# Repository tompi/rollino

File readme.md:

Rollino
=======

An attempt to make a cheap, solid and low profile DIY finger trackball.

The ball floats just 1 mm above the table on three ceramic support balls.
Two PMW3610 sensors look up at the ball from below its equator, placed so
their lines of sight are orthogonal (X, Y and twist are all observable);
their boards lie on their sides in a low ring round the back half of the
ball, each behind a printed cover that follows the ball and has a window for
the lens. A Seeed XIAO nRF52840 running ZMK lies flat in a low pod that swells out of the rim in front of
the ball, soldered upside down onto a base PCB that sits in a groove in the
underside; an FPC ribbon runs from each sensor board to it. The 602020 LiPo
stands in the same ring, between the two sensors and away from the XIAO's
antenna, leaning against the ball at the sensor boards' tilt; its leads run
round in a groove. A cover, a separate printed part, closes the whole
underside (the battery's pocket included), held by six screws.

- `case/rollino.scad` - parametric OpenSCAD model (ball size, sensor/MCU
  placement, battery, ...). Set `part` to `assembly`, `exploded`, `hardware`, `section`,
  or `body` / `base_cover` / `sensor_cover` (print two) for the printable
  parts. `fpc_check`, `wall_check` and `usb_check` should come out empty:
  there is room to pull the ribbons through, no cavity comes too close to
  the outside (`wall_check` does show the open end of the USB plug's recess),
  and the biggest USB-C plug the spec allows (12.35 x 6.5 mm overmold) goes
  in, 0.35 mm clear of the table.
- `case/renders/` - preview renders: `case/render_previews.sh` (OpenSCAD) and
  `case/render_exploded.sh` (Blender, with KiCad's 3D models of the boards:
  the assembled and the exploded view).
- `pcb/` - KiCad projects for the sensor boards and the base board: schematics
  and routed boards, generated from the case model (see [pcb/readme.md](pcb/readme.md)).

- [parts.md](parts.md) - everything to order for one Rollino.
- `datasheets/` - component datasheets. The PMW3610 datasheet is available
  [here](https://www.epsglobal.com/Media-Library/EPSGlobal/Products/files/pixart/PMW3610DM-SUDU.pdf?ext=.pdf).

Firmware
--------

ZMK, built by GitHub Actions on every push (download `firmware.zip` from the
run, then double-tap the XIAO's reset and copy the `.uf2` onto it: its
button faces down, and the cover has a hole under it for a paper clip). It's
a standalone Bluetooth/USB mouse.

- `zmk/boards/shields/rollino/` - the shield: pins, the two PMW3610 sensors
  (Zephyr's driver), three optional buttons.
- `zmk/src/ball_fusion.c` - combines the two sensors: each one only sees the
  ball's surface sliding past in its own tilted plane; together they give the
  ball's whole rotation. Rolling moves the pointer (as if the finger on top
  dragged it), twisting about the vertical axis scrolls.
- `config/rollino.keymap` - the buttons: left, middle, right click.

**Bluetooth profiles, without buttons.** It keeps three profiles (hosts).
Wiggle the ball - twist it quickly back and forth, a flick of about 20
degrees each way, with no pause - and it acts when you stop:

- 6 to 11 flicks (about a second): switch to the next profile. One that has
  no host yet advertises, so a new computer can pair with it.
- 12 or more (two seconds or so): forget the current profile's host and
  advertise again, to pair it afresh.

Scrolling stops from the fourth flick, so the page doesn't jump about.
Slow scrolling back and forth never adds up to a gesture (a flick more
than 0.4 s after the last starts the count again). The thresholds are the
`gesture-*` properties of the shield's `ball_fusion` node. To forget every
host at once, flash the `settings_reset` firmware from the same build, then
`rollino` again.

| XIAO pin | Use |
|----------|-----|
| D4 | SCLK, both sensors |
| D5 | SDIO, both sensors (SPI MOSI and MISO on the same pin) |
| D7 | NCS, right sensor |
| D6 | NCS, left sensor |
| D8 | MOTION, right sensor |
| D2 | MOTION, left sensor |
| D0, D1, D9 | optional buttons to GND: left, middle, right click |
| D3, D10 | free |

**Calibrating the sensors' orientation.** The fusion needs to know which way
each sensor's X axis points (`rotation` in the shield's `ball_fusion` node,
plus the sensor's `invert-x` / `invert-y`), which depends on how the chip
sits on the sensor PCB. The two boards are the same, lying on their sides
and turned half a turn from each other, so the two rotations differ by 180
(90 and 270 to start with). Roll the ball right: the pointer should go right;
towards you: down; twist it: scroll, with no drift. If one direction is off,
try one sensor at a time (cover the other's lens) and fix its rotation /
inversion until rolling right moves the pointer mostly right.

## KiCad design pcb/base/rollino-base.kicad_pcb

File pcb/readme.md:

Rollino PCBs
============

Two KiCad 8 projects, generated from the case model: board outlines, and
where the XIAO, the FPC connectors and the screw holes go, all come from
`case/rollino.scad`.

Rebuild them after changing the case (KiCad's own Python; Freerouting 1.5,
Java, Blender 3.x and ImageMagick for routing and rendering):

```
PY=/Applications/KiCad/KiCad.app/Contents/Frameworks/Python.framework/Versions/Current/bin/python3
$PY pcb/gen/generate.py     # schematics, footprints placed on their nets, the tracks that matter laid
$PY pcb/gen/route.py        # Freerouting routes the rest, GND poured on both layers and stitched
pcb/gen/render_pcbs.sh      # the renders above, the layout images and schematic PDFs
```

They overwrite the projects, so make changes in the scripts rather than the
KiCad files, or stop using them once you start editing the boards by hand.

Both boards are routed (0.2 mm tracks, wider where it matters, 0.15 mm
clearance, 0.3 mm from the edges, 0.6/0.3 mm vias) and pass DRC with nothing
to report, warnings included (`kicad-cli pcb drc --schematic-parity
--severity-all`); the schematics pass ERC. `route.py` checks that itself: it
only saves a board with nothing left unconnected and nothing for the DRC to
report, and fails otherwise. The sensor board's references are on its fab
layer only, as are the base board's test points' (their labels name them):
the silkscreen has no room for them.

Freerouting 1.5 can't start a track from the base board's FPC connectors
(their pads are 10 degrees off the board's axes) and would leave them
unconnected, so `generate.py` lays a short track out of each pad and
`route.py` has Freerouting join those up instead.

Sensor board (`sensor/`, two needed)
--------------------------------------

[Schematic (PDF)](sensor/rollino-sensor-schematic.pdf)

The same board for both sensors. It lies on its side (the chip's long axis
horizontal, the connector end towards the front of the case), so the left
one is turned half a turn from the right one. It's screwed into its pod from
the ball side with two M2 screws, chip side out, lens towards the ball; the
case's pocket matches its outline, ear included, and a printed cover with a
window for the lens goes in on top of it, under the same two screws.

- PMW3610DM-SUDU + LM18-LSI lens: circuit and footprint (with the lens cutout)
  after [badjeff/pmw3610-pcb](https://github.com/badjeff/pmw3610-pcb)
  (CERN-OHL-P-2.0)
- TPS7A0518 1.8 V LDO for the sensor's core: 1 uA quiescent, instead of the
  ~34 uA of the TLV74318 used there, which would otherwise draw more than the
  resting sensor
- each capacitor is by the pin it serves, on a short wide track laid by
  `generate.py`: C4 under the charge pump's two pins and C6/C7 under VCP's
  (PixArt asks for those tracks to be under 5 mm long and over 20 mil wide:
  they are 2 to 4 mm and 0.6 mm), C5 under the laser's, C2/C1 under VDD's,
  C8/C3 by VDDIO's and C9 against the regulator's output; their grounds are
  a rail from pin 11 with vias to the pour on the back
- 1.8 V goes from the regulator to VDD on the back, round the lens cutout's
  short end
- TP1 (+1V8) and TP2 (GND): pads for a meter when bringing a board up
- FH12-6S-0.5SH FPC connector at the board's front end, mouth facing off
  the edge, so the ribbon is easy to push in and latch before the board goes
  into its pod; the ribbon then bends back over the connector and the chip,
  where it is folded (a 45 degree crease, flat) to run down the slope, past
  the board's low edge, to the base board (the pod has room for the bend and
  a channel for the ribbon)
- two mounting holes either side of the lens: H1 in an ear on the back end,
  on the board's centre line, and H2 beside the connector. Nothing sticks
  out of one long side only, so the board fits either way up the slope
- the ribbon's way down through the pod is roomy (5.5 mm wide, the case
  checks it with a 1.5 mm thick stand-in: `part="fpc_check"` must be empty),
  so its free end can be fed through from the pod or from underneath before
  the boards go in
- the regulator's EN is tied to its VIN by a fixed track between its rows of
  pins (route.py keeps it): the board edge leaves no other way in
- a small ROLLINO logo in bare copper on the back, between the front edge
  and the lens
- board frame: origin on the optical axis, x along the chip (towards the
  back of the case), y across it

Base board (`base/`)
--------------------

[Schematic (PDF)](base/rollino-base-schematic.pdf)

Lies in a groove in the case's underside, under the front pod and a little
way round each side, held (with the cover under it) by four M2 screws.

- Seeed XIAO nRF52840 soldered **upside down** by its castellated edges: its
  parts (USB-C included) hang through the cutout into a pocket in the cover;
  its battery pads face up, and the LiPo's leads (which come round from the
  battery's pocket in the ring at the back of the case, and up behind the XIAO's far
  corner) solder straight onto them
- J1 (right sensor) and J2 (left) at the band's ends, along it, mouths facing
  the ribbons coming along the channel in the case's underside
- J3-J5: optional buttons (left, middle, right click), a pair of through
  holes each (2.54 mm apart, for wires or a header): the square one the
  button's line, the round one GND. Left and right on the branches, in
  front of the screws; middle beside the XIAO's far left corner (the strip
  behind the XIAO is the antenna's)
- the ROLLINO logo is bare copper (no solder mask) on the back, beside the
  XIAO
- the XIAO's chip antenna is at its far end, inside the notch and a fraction
  of a millimetre from this board: the pours stay off the strip between the
  notch and the ball's hole and away from the XIAO's last few millimetres,
  and the four tracks that have to cross that strip (the bus and the supply,
  to the left sensor) keep a millimetre from the notch; the supply's two,
  the only thing joining the two halves' ground, are laid by `generate.py`
  on the back
- pins as in the firmware (`zmk/boards/shields/rollino/rollino.overlay`): the
  bus on D4/D5, the XIAO's only pins that aren't next to its radio, and each
  sensor's own lines and each button on the pins of their side

Ribbons
-------

Two 6-way 0.5 mm FFCs, 50 mm long (the stock length: 40 mm ones are hard
to find), with same-side (type A) contacts. Each leaves its sensor board's
connector towards the front, bends back over the connector and the chip, and
is folded there (a 45 degree crease, pressed flat) to run down the slope
over the chip's back. Past the board's low edge it turns in under the board,
lying on the cover, and with a second crease turns towards the front, along
a channel in the case's underside, straight into the base board's connector
at the end of the band; the case model sets where that is from the cable's
length (`fpc_len`). The U-turn, the fold and the crease each turn the ribbon
over, which leaves the face that met the sensor board's connector facing the
base board's: hence type A. The pins at each end are numbered from the
ribbon's path so that each signal meets itself: put the ribbon in, fold it
and lay it in its channel before the base board goes up.

Parts
-----

| Board | Ref | Part |
|-------|-----|------|
| sensor (x2) | U1 | PMW3610DM-SUDU + LM18-LSI lens |
| | U2 | TPS7A0518PDBVR (SOT-23-5) |
| | J1 | Hirose FH12-6S-0.5SH (or JUSHUO AFC01-S06FCA) |
| | R1 | 10k 0603 |
| | C1 | 3.3 uF 0603 |
| | C2, C3 | 100 nF 0603 |
| | C4 | 100 nF X7R 0603 |
| | C5 | 10 nF 0603 |
| | C6 | 10 uF X7R 0603 |
| | C7 | 10 nF X7R 0603 |
| | C8, C9 | 1 uF 0603 |
| base | U1 | Seeed XIAO nRF52840 (not Sense) |
| | J1, J2 | Hirose FH12-6S-0.5SH (or JUSHUO AFC01-S06FCA) |

`lib/` has the project's own symbols, footprints and 3D models (the XIAO's
from Seeed's, the PMW3610 and its lens as plain blocks); everything else is
from KiCad's standard libraries.

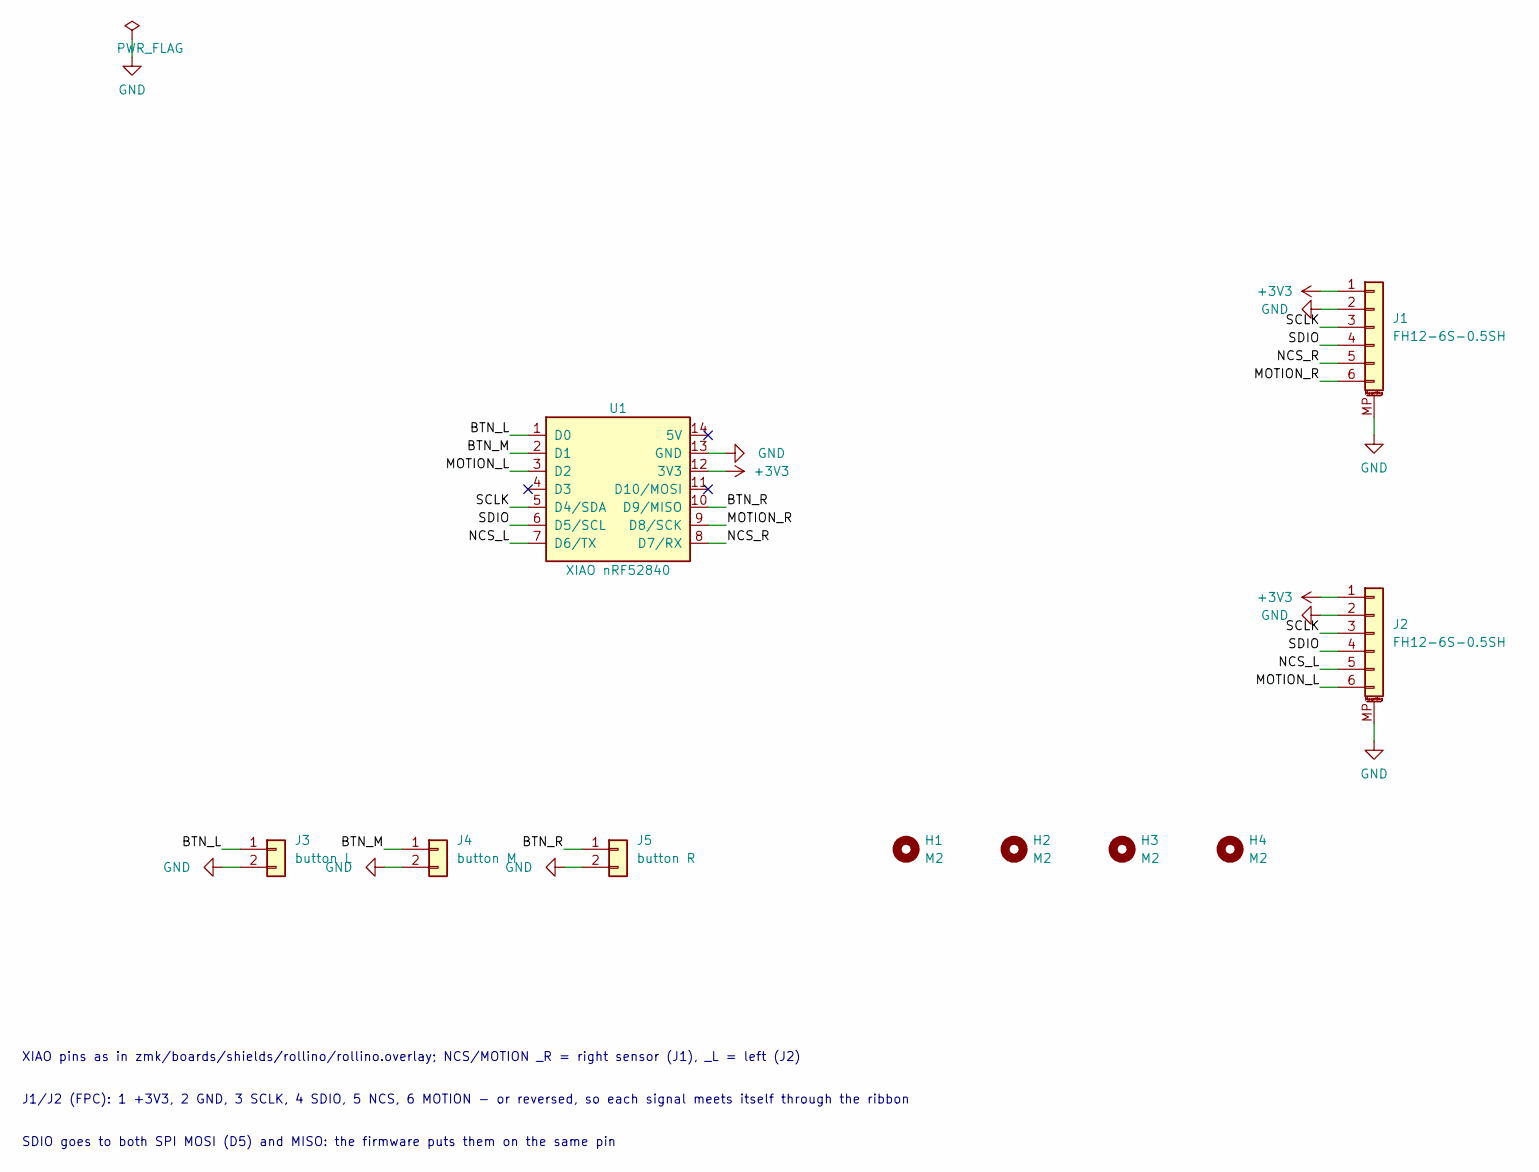
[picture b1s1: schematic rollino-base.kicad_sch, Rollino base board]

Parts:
H1, H2, H3, H4: M2; MountingHole_2.2mm_M2
J1, J2: FH12-6S-0.5SH; Hirose_FH12-6S-0.5SH_1x06-1MP_P0.50mm_Horizontal
J3: button L; ButtonPads_1x02_P2.54mm
J4: button M; ButtonPads_1x02_P2.54mm
J5: button R; ButtonPads_1x02_P2.54mm
U1: XIAO nRF52840; XIAO_nRF52840_upside_down

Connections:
+3V3: J1.1, J2.1, U1.12 (3V3)
/BTN_L: J3.1, U1.1 (D0)
/BTN_M: J4.1, U1.2 (D1)
/BTN_R: J5.1, U1.10 (D9/MISO)
/MOTION_L: J2.6, U1.3 (D2)
/MOTION_R: J1.6, U1.9 (D8/SCK)
/NCS_L: J2.5, U1.7 (D6/TX)
/NCS_R: J1.5, U1.8 (D7/RX)
/SCLK: J1.3, J2.3, U1.5 (D4/SDA)
/SDIO: J1.4, J2.4, U1.6 (D5/SCL)
GND: J1.2, J1.MP (MountPin), J2.2, J2.MP (MountPin), J3.2, J4.2, J5.2, U1.13 (GND)

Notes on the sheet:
XIAO pins as in zmk/boards/shields/rollino/rollino.overlay; NCS/MOTION _R = right sensor (J1), _L = left (J2)
J1/J2 (FPC): 1 +3V3, 2 GND, 3 SCLK, 4 SDIO, 5 NCS, 6 MOTION - or reversed, so each signal meets itself through the ribbon
SDIO goes to both SPI MOSI (D5) and MISO: the firmware puts them on the same pin

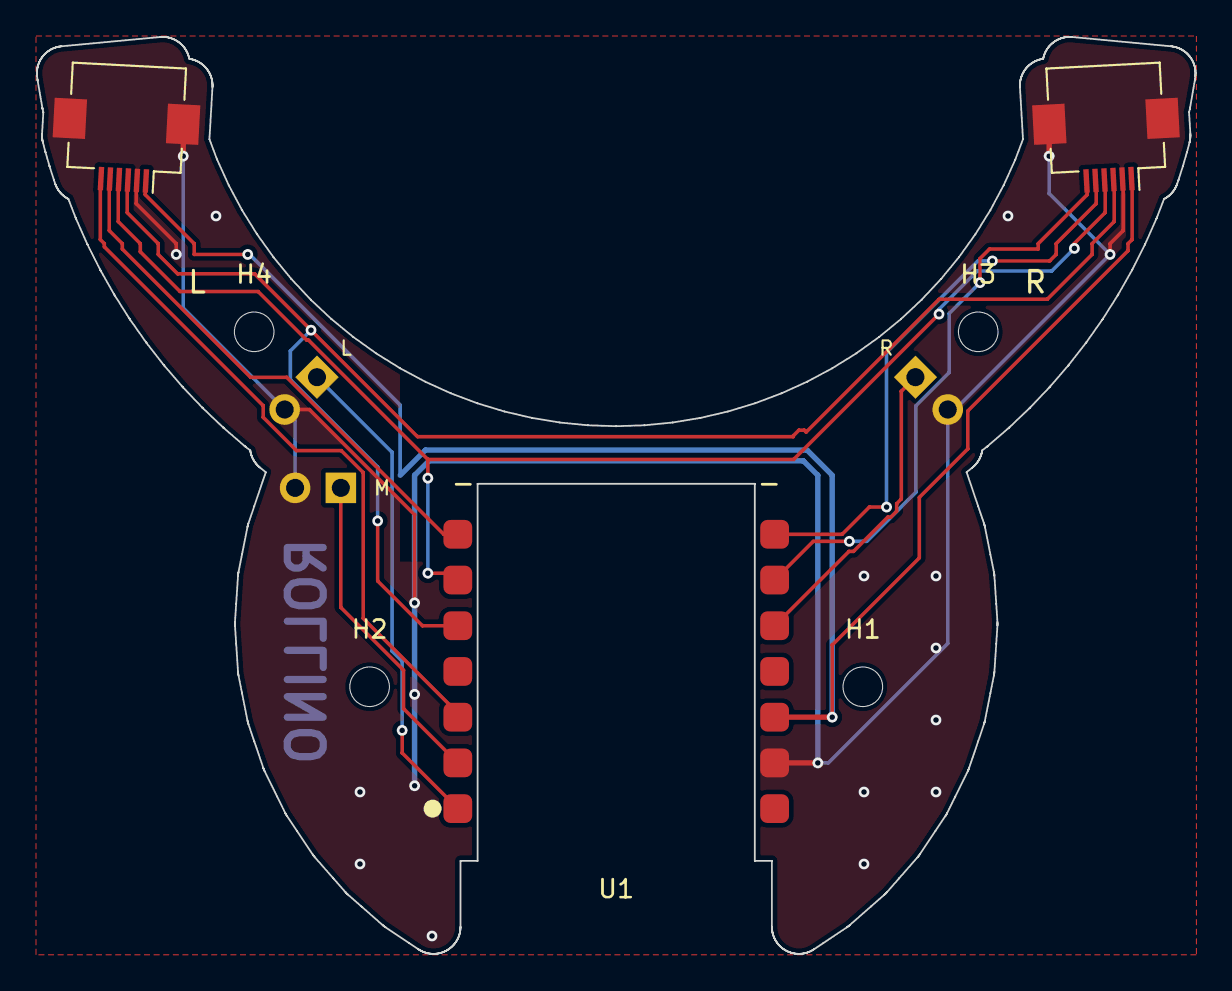
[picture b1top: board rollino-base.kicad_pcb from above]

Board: 2 copper layers, 64.4 x 50.9 mm, 10 parts (0 on the bottom side), 11 nets.

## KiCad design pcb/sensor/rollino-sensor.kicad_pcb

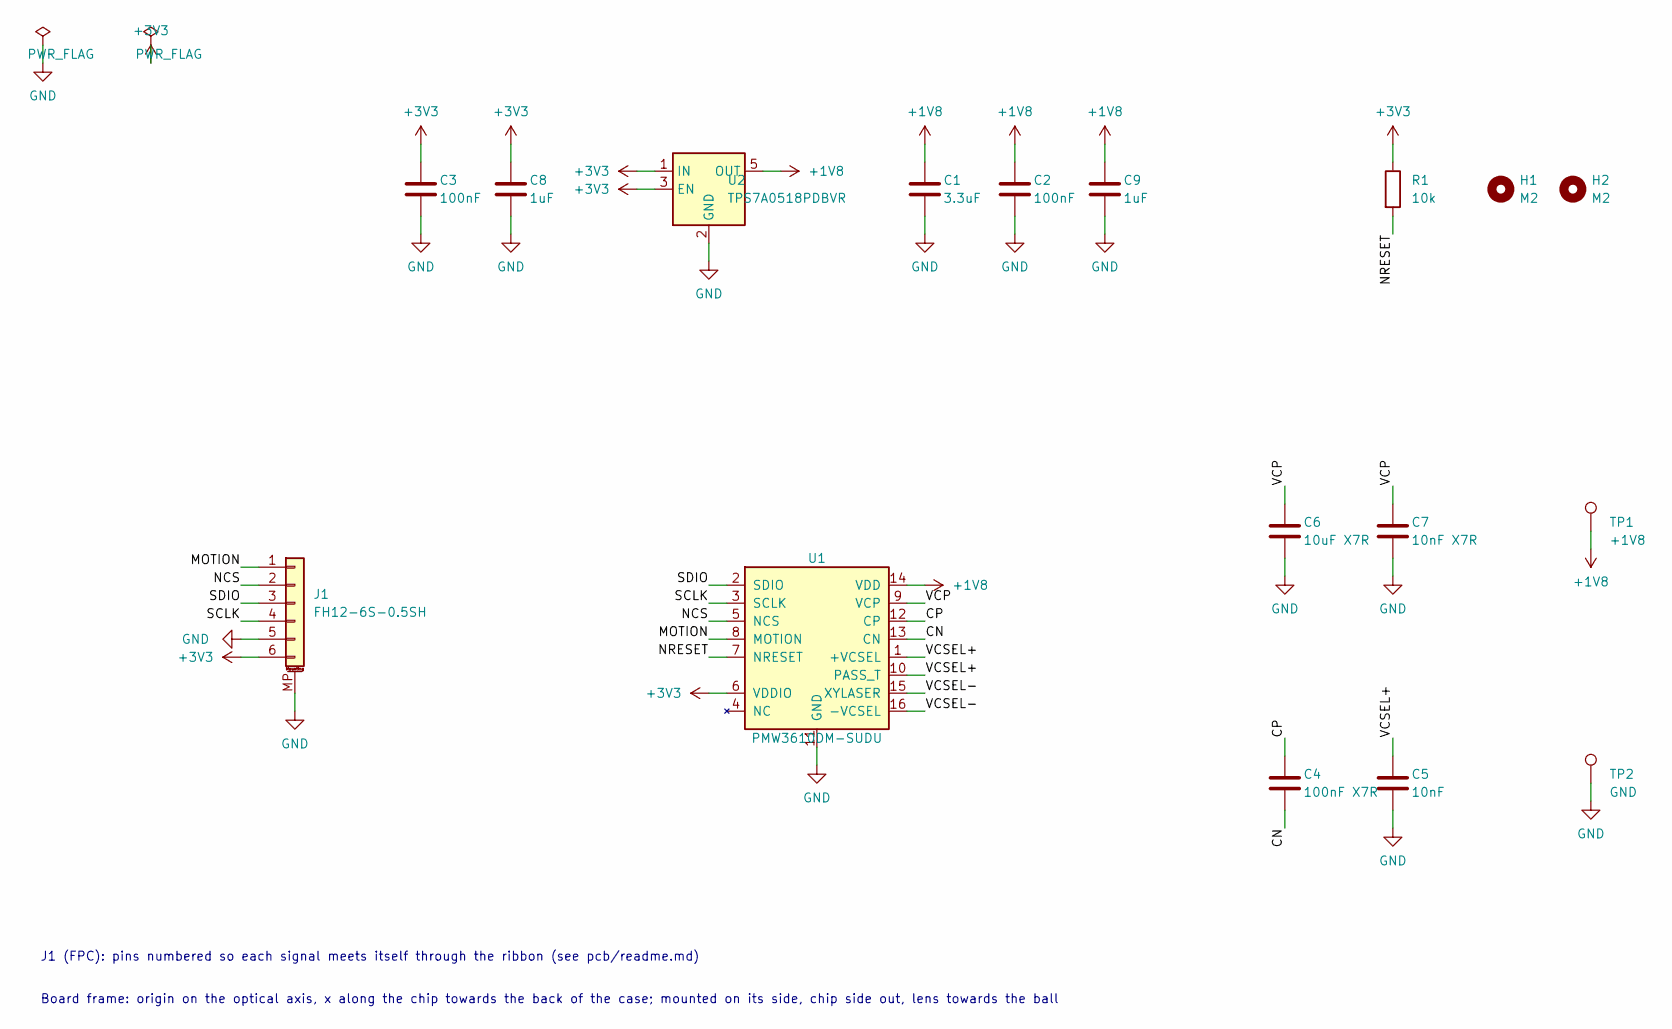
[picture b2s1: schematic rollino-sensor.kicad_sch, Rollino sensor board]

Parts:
C1: 3.3uF; C_0603_1608Metric
C2, C3: 100nF; C_0603_1608Metric
C4: 100nF X7R; C_0603_1608Metric
C5: 10nF; C_0603_1608Metric
C6: 10uF X7R; C_0603_1608Metric
C7: 10nF X7R; C_0603_1608Metric
C8, C9: 1uF; C_0603_1608Metric
H1, H2: M2; MountingHole_2.2mm_M2
J1: FH12-6S-0.5SH; Hirose_FH12-6S-0.5SH_1x06-1MP_P0.50mm_Horizontal
R1: 10k; R_0603_1608Metric
TP1: +1V8; TestPoint_Pad_D1.0mm
TP2: GND; TestPoint_Pad_D1.0mm
U1: PMW3610DM-SUDU
U2: TPS7A0518PDBVR; SOT-23-5

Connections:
+1V8: C1.1, C2.1, C9.1, TP1.1, U1.14 (VDD), U2.5 (OUT)
+3V3: C3.1, C8.1, J1.6, R1.1, U1.6 (VDDIO), U2.1 (IN), U2.3 (EN)
/CN: C4.2, U1.13 (CN)
/CP: C4.1, U1.12 (CP)
/MOTION: J1.1, U1.8 (MOTION)
/NCS: J1.2, U1.5 (NCS)
/NRESET: R1.2, U1.7 (NRESET)
/SCLK: J1.4, U1.3 (SCLK)
/SDIO: J1.3, U1.2 (SDIO)
/VCP: C6.1, C7.1, U1.9 (VCP)
/VCSEL+: C5.1, U1.1 (+VCSEL), U1.10 (PASS_T)
/VCSEL-: U1.15 (XYLASER), U1.16 (-VCSEL)
GND: C1.2, C2.2, C3.2, C5.2, C6.2, C7.2, C8.2, C9.2, J1.5, J1.MP (MountPin), TP2.1, U1.11 (GND), U2.2 (GND)

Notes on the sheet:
J1 (FPC): pins numbered so each signal meets itself through the ribbon (see pcb/readme.md)
Board frame: origin on the optical axis, x along the chip towards the back of the case; mounted on its side, chip side out, lens towards the ball

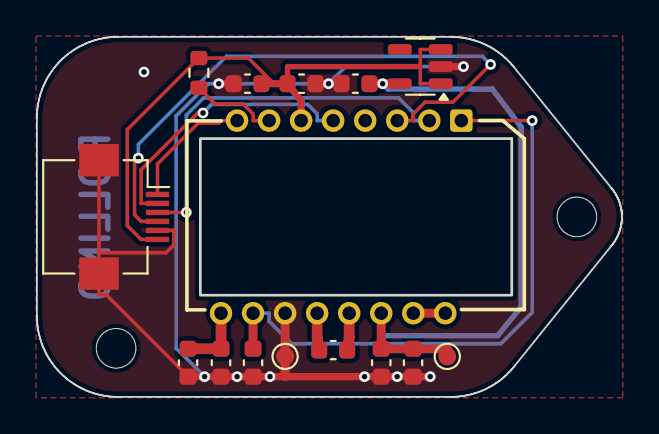
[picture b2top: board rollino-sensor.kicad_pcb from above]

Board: 2 copper layers, 32.5 x 20.0 mm, 17 parts (0 on the bottom side), 13 nets.

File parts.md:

Parts list
==========

Everything for one Rollino; quantities are totals (it has two sensor boards).
The case itself (`body`, `base_cover` and two of `sensor_cover` in
`case/rollino.scad`) is printed.

PCBs
----

| Qty | Board | Notes |
|-----|-------|-------|
| 2 | sensor board (`pcb/sensor/`) | 2 layers, 1.6 mm FR4; has a cutout for the lens |
| 1 | base board (`pcb/base/`) | 2 layers, 1.6 mm FR4; has a cutout for the XIAO's parts |

0.2 mm tracks, 0.15 mm clearance, 0.3 mm drills: any fab's standard process.
Both have a bare-copper logo, so pick ENIG (or HASL) rather than bare copper
finish.

Electronics
-----------

| Qty | Part | Where | Notes |
|-----|------|-------|-------|
| 1 | Seeed XIAO nRF52840 (not Sense) | base U1 | soldered upside down by its edge pads |
| 2 | PixArt PMW3610DM-SUDU | sensor U1 | |
| 2 | LM18-LSI lens | under each PMW3610 | the PMW3610's lens; often sold with it |
| 2 | TI TPS7A0518PDBVR (1.8 V LDO, SOT-23-5) | sensor U2 | |
| 4 | Hirose FH12-6S-0.5SH(55) (or JUSHUO AFC01-S06FCA) | sensor J1, base J1/J2 | 6-pin, 0.5 mm FPC connector |
| 2 | 6-way FFC, 0.5 mm pitch, 50 mm, **same-side (type A) contacts** | sensor to base | for 0.3 mm thick FPC connectors (FH12); 50 mm is the stock length |
| 1 | LiPo 602020, about 200 mAh, with protection board | pocket in the ring at the back of the case | up to 22 x 20 x 6.5 mm; goes in from below, protection board down; its leads run round in a groove to the XIAO's battery pads and need to be about 90 mm long (extend them if they are shorter) |

Passives, all 0603, for both sensor boards together (10 V or more; the 10 uF
X7R is the scarce one, for instance Murata GRM188Z71A106KA73D, and 6.3 V
will do for it: PixArt asks for 6.3 to 16 V, 10 %):

| Qty | Value | Where (on each sensor board) |
|-----|-------|------------------------------|
| 6 | 100 nF X7R | C2, C3, C4 |
| 4 | 10 nF X7R | C5, C7 |
| 4 | 1 uF | C8, C9 |
| 2 | 3.3 uF | C1 |
| 2 | 10 uF X7R | C6 |
| 2 | 10 k resistor | R1 |

Optional: up to three momentary switches for left, middle and right click,
wired to the base board's J3-J5 (a pair of through holes each: the square
one the button's line, the round one GND).

Mechanical
----------

| Qty | Part | Notes |
|-----|------|-------|
| 1 | 55 mm trackball ball | the size Kensington's trackballs use (Expert Mouse, SlimBlade), sold as replacements |
| 3 | 3 mm ceramic bearing balls (ZrO2 or Si3N4) | the ball's supports; get a few spares |
| 6 | M2 x 8 countersunk thread-forming screws for plastic | through the cover (four of them through the base board too) into the case |
| 4 | M2 x 10 thread-forming screws for plastic, pan head (up to 3.8 mm across) | two through each sensor cover and board |

Screw lengths are from the model: the cover and base board are 5.2 mm
together, with 4.5 mm pilot holes above them (the two screws beside the
battery go through the cover only, into holes as much deeper); each sensor
cover is 3.5 mm under the screw heads and each sensor board 1.6 mm, with a
5.5 mm pilot hole behind it (without the covers, M2 x 6 would do).

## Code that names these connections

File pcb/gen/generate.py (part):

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
# ---------------------------------------------------------------- the boards

FPC_PINS = ["+3V3", "GND", "SCLK", "SDIO", "NCS", "MOTION"]
FPC_FP = "Connector_FFC-FPC:Hirose_FH12-6S-0.5SH_1x06-1MP_P0.50mm_Horizontal"
FPC_VALUE = "FH12-6S-0.5SH"
# with a pin for the connector's mounting tabs, which go to GND
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        # on the other side each is upright under the pin it serves, that pad
        # towards the pin and its ground along the board's edge
        ("C6", "Device:C", "10uF X7R", C0603, (200, 100), {"1": "VCP", "2": "GND"}, (-12.0, BOT), 270),
        ("C7", "Device:C", "10nF X7R", C0603, (215, 100), {"1": "VCP", "2": "GND"}, (pin(9)[0], BOT), 270),
        ("C5", "Device:C", "10nF", C0603, (215, 135), {"1": "VCSEL+", "2": "GND"}, (pin(10)[0], BOT), 270),
        # (lying under the charge pump's two pins, a pad under each)
        ("C4", "Device:C", "100nF X7R", C0603, (200, 135), {"1": "CP", "2": "CN"}, (c4, -TOP), 0),
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    # The tracks that matter are laid here (locked: route.py keeps them) and
    # Freerouting does the rest. PixArt wants CP, CN and VCP's under 5 mm
    # long and over 20 mil wide: straight from each pin to its capacitor
    b.track("VCP", [pin(9), (pin(9)[0], BOT - PAD), (-12.0, BOT - PAD)], 0.6)
    b.track("CP", [pin(12), (pin(12)[0], 6.7), (c4 - PAD, -TOP)], 0.6)
    b.track("CN", [pin(13), (pin(13)[0], 6.7), (c4 + PAD, -TOP)], 0.6)
    b.track("VCSEL+", [pin(10), (pin(10)[0], BOT - PAD)], 0.5)
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    # keep for low frequencies (they are away from the radio), and each
    # sensor's own lines and the buttons are on the pins of their side, so
    # only the bus and the supply cross from one side to the other
    xiao_pins = {"1": "BTN_L", "2": "BTN_M", "3": "MOTION_L", "4": None, "5": "SCLK", "6": "SDIO",
                 "7": "NCS_L", "8": "NCS_R", "9": "MOTION_R", "10": "BTN_R", "11": None,
                 "12": "+3V3", "13": "GND", "14": None}
    u = sch.symbol("U1", "rollino:XIAO_nRF52840", "XIAO nRF52840", "rollino:XIAO_nRF52840_upside_down",
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        ref = "J%d" % (i + 1)
        ux, uy = math.cos(math.radians(ang)), -math.sin(math.radians(ang))  # board direction of the mouth
        rot = mouth_rotation(ux, uy)
        pins = fpc_pins(rot, e, {"NCS": "NCS_" + side, "MOTION": "MOTION_" + side})
        u = sch.symbol(ref, FPC_SYMBOL, FPC_VALUE, FPC_FP, (215, 70 + 45 * i), pins)
        mid = (FPC_TAIL + FPC_MOUTH) / 2
        fx, fy = kp(foot)
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        b.footprint("MountingHole:MountingHole_2.2mm_M2", "H%d" % (i + 1), "M2", kp(w), sym_uuid=u)

    sch.flag("GND", (40, 30))
    sch.text("XIAO pins as in zmk/boards/shields/rollino/rollino.overlay; NCS/MOTION _R = right sensor (J1), _L = left (J2)", (25, 175))
    sch.text("J1/J2 (FPC): 1 +3V3, 2 GND, 3 SCLK, 4 SDIO, 5 NCS, 6 MOTION - or reversed, so each signal meets itself through the ribbon", (25, 181))
    sch.text("SDIO goes to both SPI MOSI (D5) and MISO: the firmware puts them on the same pin", (25, 187))
    sch.write(os.path.join(d, name + ".kicad_sch"))
    # the logo in bare copper on the back, beside the XIAO on the left,
    # outside the screw hole there; route.py keeps the tracks out of its way
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
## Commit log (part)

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2024-09-14 Initial commit: component specs

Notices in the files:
pcb/gen/generate.py:
PMW3610: badjeff's footprint (github.com/badjeff/pmw3610-pcb, CERN-OHL-P
parts and their libraries:
PMW3610DM-SUDU 16-pin molded lead-frame DIP, with the LM18-LSI lens cutout; optical centre at (2.988, 0). From github.com/badjeff/pmw3610-pcb (CERN-OHL-P-2.0)
